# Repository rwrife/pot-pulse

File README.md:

# Pot Pulse

USB-powered ESP32-C3 plant-shelf monitor for home growers to track soil moisture, light, and microclimate trends in a local dashboard without cloud accounts or automatic watering.

## Motivation
Houseplant care is mostly guesswork between watering days. People often overwater because they cannot see trend data (light, moisture, humidity) across multiple pots in one place.

## Target users
- Home plant hobbyists with 1–20 potted indoor plants
- Small office/shared-space plant caretakers
- Makers who want a safe, low-voltage, locally controlled monitoring tool

## Concrete use cases
1. Compare morning/evening light exposure per shelf position.
2. Track soil moisture drop rate after watering to tune intervals.
3. Spot dry microclimates near windows/vents before plants decline.
4. Export a local history snapshot for seasonal care adjustments.

## Intended end-to-end workflow
1. Assemble device (SELV USB only) and connect sensors for each monitored pot zone.
2. Join device to local network (or direct USB setup mode).
3. Name shelves/zones in the companion app.
4. Calibrate moisture probes with dry/wet reference points.
5. Review live status + trend charts; set local reminder thresholds.
6. Export CSV/JSON snapshots for personal records.

## MVP features
- ESP32-C3 firmware with periodic sampling (moisture, light, temp/humidity)
- Local-first companion web app (mobile + desktop browsers)
- Per-zone calibration profiles and health-state bands (informational only)
- On-device ring buffer with timestamped readings
- Local network API for status/history/export
- USB recovery/provisioning flow
- Versioned backup/restore of settings and zone metadata

## Non-goals (MVP)
- Automatic watering, relays, or pumps
- Any mains-voltage control path
- Cloud account requirement or remote telemetry service
- Plant diagnosis/treatment claims
- Outdoor/weatherproof deployment

## Privacy, permissions, and data ownership
- Local-first by default: data stored on device and exported by user action.
- No required cloud service.
- Companion app only requests local-network/browser storage permissions needed for setup, caching, and export.
- User can delete local history and reset device from settings.

## Safety limits
- Prototype scope is **SELV USB power only (5V)**.
- Monitoring only; no high-power actuators.
- Not a life-safety, agricultural compliance, or medical system.

## Source tree and artifact policy
Hardware implementation is delivered as editable KiCad source files (not image-only schematics):

- `hardware/kicad/pot-pulse.kicad_pro`
- `hardware/kicad/pot-pulse.kicad_sch`
- `hardware/kicad/pot-pulse.kicad_pcb`

Final BOM source of truth will live in KiCad schematic symbol properties and be exported to tracked `bom/bom.csv`.

## Current status
- ✅ Repository scaffold and execution backlog created
- ✅ MVP architecture, interface ownership, non-goals, and risk baseline documented in [`docs/architecture.md`](docs/architecture.md)
- ✅ Datasheet-backed critical component selection documented in [`hardware/component-selection.md`](hardware/component-selection.md)
- ✅ Editable KiCad project, DRC/ERC evidence, and pad-net cross-check tooling under [`hardware/kicad/`](hardware/kicad/)
- ✅ Firmware MVP with repeatable native tests and ESP32-C3 builds under [`firmware/`](firmware/)
- ✅ Companion app MVP with repeatable typecheck/test/build under [`app/`](app/)
- ✅ Integration bring-up + assembly docs, evidence matrix, and fabrication preview bundle under [`docs/`](docs/)
- 🚧 Production-ready fabrication release still blocked by open PCB unconnected items (see `docs/evidence/2026-09-14/drc.json`)

## Milestones
1. Architecture and risk baseline
2. Datasheet-backed component selection
3. KiCad schematic and ERC
4. Schematic-source BOM and non-schematic procurement tracking
5. PCB layout and DRC
6. Firmware MVP with repeatable build/tests
7. Companion app MVP with local export
8. Integration docs and fabrication-ready release package

See [`PLAN.md`](PLAN.md) for the authoritative issue dependency graph and exit gates.

## Integration handoff docs

- Bring-up procedure: [`docs/bring-up.md`](docs/bring-up.md)
- Assembly sequence and checks: [`docs/assembly.md`](docs/assembly.md)
- Evidence classification: [`docs/evidence-matrix.md`](docs/evidence-matrix.md)
- Fabrication/release workflow: [`docs/release-artifacts.md`](docs/release-artifacts.md)
- Explicit media placeholders: [`docs/media-placeholders.md`](docs/media-placeholders.md)

## Development quickstart
### Firmware
- Toolchain: PlatformIO (ESP-IDF framework)
- Target: ESP32-C3 dev module + custom carrier pin map

### Companion app
- TypeScript + Vite + local-first PWA behavior
- Connect to device over local HTTP/WebSocket

### Hardware
- KiCad 9 project under `hardware/kicad/`
- BOM exported to `bom/bom.csv`

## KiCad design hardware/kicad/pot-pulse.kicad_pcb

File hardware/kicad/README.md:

# Pot Pulse KiCad project

This directory contains the editable KiCad 9 project for the USB-powered Pot Pulse four-zone sensor node: first-pass schematic (issue #3) and first-pass PCB (issue #5).

## Files

- `pot-pulse.kicad_pro` — KiCad project settings.
- `pot-pulse.kicad_sch` — editable schematic source of truth.
- `pot-pulse.kicad_pcb` — editable first-pass PCB (generated by `build_pcb.py`, routed via FreeRouter, DRC-adjudicated).
- `lib/pot-pulse.kicad_sym` — project symbols whose pin maps were transcribed from the manufacturer documents cited in `../component-selection.md`.
- `lib/pot-pulse.pretty/` — project land patterns (ESP32-C3-MINI-1, VEML7700) transcribed from the datasheets cited in `../component-selection.md`; generated by `generate_footprints.py`.
- `fp-lib-table` / `sym-lib-table` — project library registration so the board opens on any machine with KiCad 9.
- `generate_schematic.py` — reproducible first-capture generator; the generated schematic remains editable in KiCad.
- `validate_schematic.py` — static acceptance checks for required parts, properties, nets, pin mappings, test access, and the native ERC summary.
- `netlist_to_json.py` — exports `reports/pcb-input/{netlist,components}.json` (placement/routing input data derived from the schematic netlist).
- `build_pcb.py` — generates `pot-pulse.kicad_pcb` through the pcbnew API (outline, placement table with courtyard/edge asserts, net classes, RF rule areas, pours, text).
- `generate_footprints.py` — generates the project land patterns from datasheet dimensions.
- `route_driver.py` — Specctra DSN export / SES import driver (import saves immediately before probing).
- `dsn_strip_inner_layers.py` — keeps the autorouter on F.Cu/B.Cu so the inner planes stay solid.
- `rip_up_dangling.py` / `rip_up_zone.py` / `rip_up_congested.py` — stranded-fragment and surgical rip-up helpers between router passes.
- `close_stubs.py` — deterministic final stub closer (collision-capsule tested; `--dry` reports LEFT pairs verbatim).
- `fill_zones.py` — headless "Fill All Zones".
- `silk_hygiene.py` — post-route silkscreen cleanup (hides dense-passive refs, shrinks TP/test refs, enforces 0.15 mm text stroke).
- `reload_probe.py` / `check_placement_vs_table.py` / `board_inventory.py` / `list_plane_tracks.py` / `lane_blockers.py` — verification probes (reload integrity, placement-vs-table drift, copper inventory, residual-gap diagnosis).
- `reports/erc.rpt` — native KiCad 9 electrical-rules report.
- `reports/schematic-analysis.txt` — supplemental static analyzer output.
- `reports/pot-pulse.net` — netlist export feeding `netlist_to_json.py`.
- `reports/drc-placement.json` — placement-stage native DRC (pre-routing).
- `reports/routing/` — per-pass DSN/SES/DRC evidence; each `passN-drc.json` is the `kicad-cli` truth for that pass.
- `reports/drc-final.json` — committed final DRC state for `pot-pulse.kicad_pcb`.

Layout intent, keepout strategy, grounding approach, assembly/testability notes, and documented first-pass gaps: `../pcb-design-notes.md`.

## Reproduce and verify

The host needs KiCad 9 symbol libraries and Python 3.11+:

```sh
python3 -m venv /tmp/pot-pulse-kicad-venv
/tmp/pot-pulse-kicad-venv/bin/pip install -r hardware/kicad/requirements.txt
KICAD_SYMBOL_DIR=/usr/share/kicad/symbols \
  /tmp/pot-pulse-kicad-venv/bin/python hardware/kicad/generate_schematic.py
kicad-cli sch erc -o hardware/kicad/reports/erc.rpt hardware/kicad/pot-pulse.kicad_sch
KICAD_SYMBOL_DIR=/usr/share/kicad/symbols \
  /tmp/pot-pulse-kicad-venv/bin/python hardware/kicad/validate_schematic.py \
  --erc hardware/kicad/reports/erc.rpt
```

The PCB steps need the `pcbnew` Python bindings (KiCad container image); all
scripts run inside `hardware/kicad/`:

```sh
kicad-cli sch export netlist pot-pulse.kicad_sch -o reports/pot-pulse.net
python3 netlist_to_json.py
python3 build_pcb.py                       # asserts courtyard/edge placement
python3 reload_probe.py                    # reload integrity + pad-net probe
python3 check_placement_vs_table.py        # board vs build_pcb.py table
python3 route_driver.py export reports/routing/passN.dsn
# host: java -Djava.awt.headless=true -jar freerouting-2.4.1.jar \
#   -de passN-2l.dsn -do passN.ses -mp 12 -gui.enabled=false   (after dsn_strip_inner_layers.py)
python3 route_driver.py import reports/routing/passN.ses
python3 rip_up_dangling.py && python3 fill_zones.py && python3 silk_hygiene.py
python3 close_stubs.py --drc reports/routing/passN-drc.json    # deterministic final stubs
kicad-cli pcb drc --severity-error --severity-warning --format json \
  --output reports/drc-final.json pot-pulse.kicad_pcb
```

The repository's headless `kicad-cli` wrapper runs KiCad 9 in a container. Committed reports are generated from the editable sources, not hand-authored.

## Evidence boundary

Schematic files provide **static schematic and native ERC evidence**. The PCB
provides **static layout + native DRC evidence plus autorouter-derived routing
provenance**. These files do not provide simulation, assembled-board, EMC,
environmental, field, or calibration evidence. RF keepout geometry is
datasheet-derived; measured RF performance is bench evidence not yet claimed.
USB full-speed impedance is not yet stackup-verified (documented gap in
`../pcb-design-notes.md`).

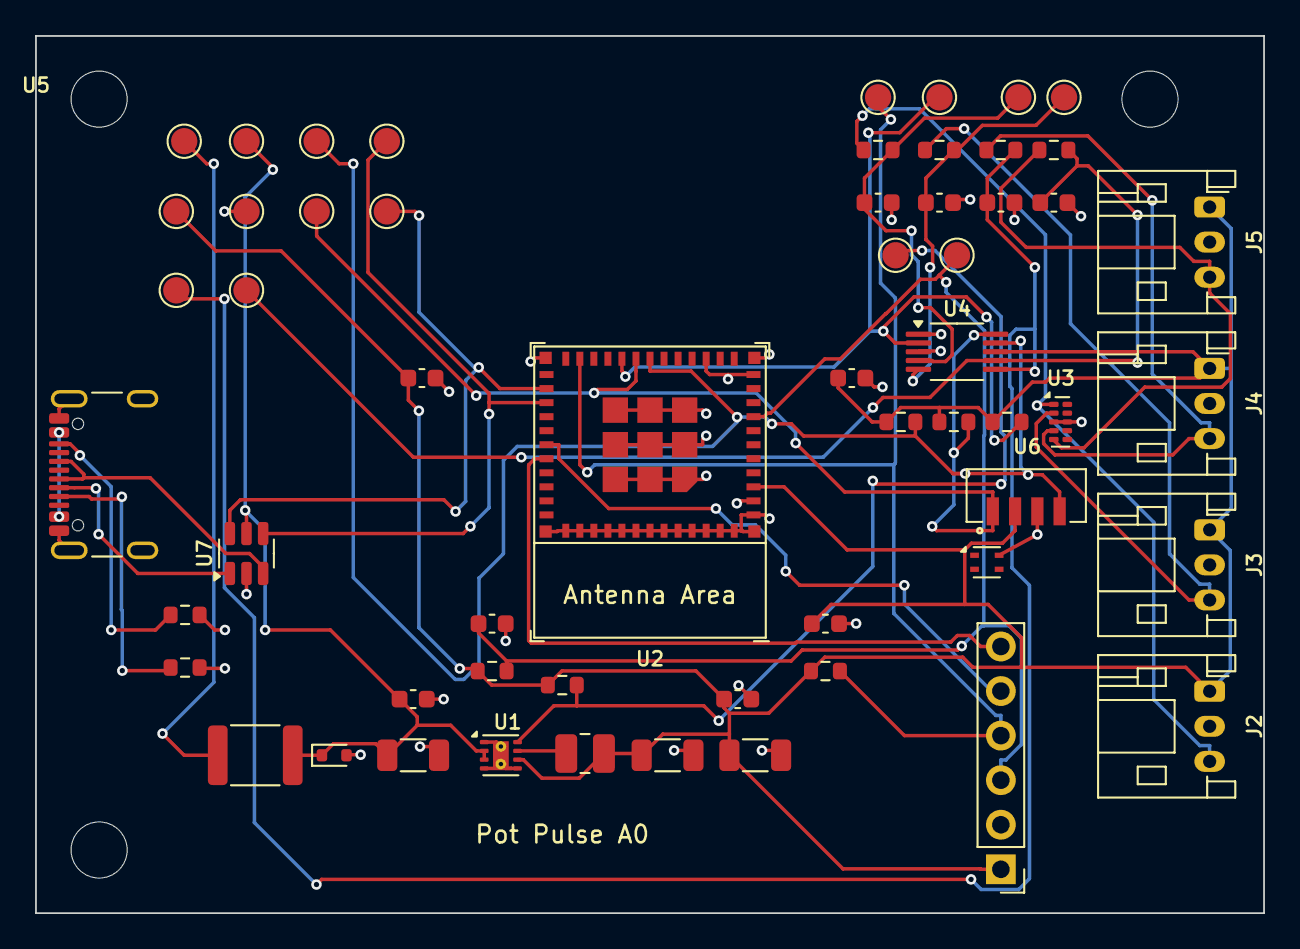
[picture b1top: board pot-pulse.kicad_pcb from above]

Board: 4 copper layers, 70.0 x 50.0 mm, 60 parts (0 on the bottom side), 27 nets.

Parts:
C1, C3, C4: C_1206_3216Metric
C2, C5, C6, C7, C8, C9, C10, C11, C12, C13: C_0603_1608Metric
D1: D_SOD-523
F1: Fuse_1812_4532Metric
J1: USB_C_Receptacle_GCT_USB4105-xx-A_16P_TopMnt_Hori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; USB_C_Receptacle_GCT_USB4105-xx-A_16P_TopMnt_Horizontal
J2, J3, J4, J5: JST_PH_S3B-PH-K_1x03_P2.00mm_Horizontal
J6: PinHeader_1x06_P2.54mm_Vertical
L1: L_1008_2520Metric
MK1, MK2, MK3: MountingHole_3.2mm_M3
R1, R2, R3, R4, R5, R6, R7, R8, R9, R10, R11, R12: R_0603_1608Metric
TP1, TP2, TP3, TP4, TP5, TP6, TP7, TP8, TP9, TP10, TP11, TP12, TP13, TP14, TP15, TP16: TestPoint_Pad_D1.5mm
U1: WSON-8-1EP_2x2mm_P0.5mm_EP0.9x1.6mm_ThermalVias
U2: ESP32-C3-MINI-1
U3: USON-10_2.5x1.0mm_P0.5mm
U4: VSSOP-10_3x3mm_P0.5mm
U5: Sensirion_DFN-4_1.5x1.5mm_P0.8mm_SHT4x_NoCentralP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; Sensirion_DFN-4_1.5x1.5mm_P0.8mm_SHT4x_NoCentralPad
U6: VEML7700
U7: SOT-23-6

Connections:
/+3V3: C3.1, C4.1, C5.1, C7.1, C8.1, C9.1, J2.1, J3.1, J4.1, J5.1, J6.1, L1.2, R3.1, R4.1, R5.1, R6.1, R7.1, R8.1, TP3.1, U1.6, U2.3, U4.8, U5.3, U6.2
/+5V_PROTECTED: C1.1, C2.1, D1.1, F1.2, TP2.1, U1.2, U1.3, U7.5
/ADC_ALERT_N: R8.2, TP12.1, U2.20, U4.2
/BOOT_GPIO9: J6.4, R7.2, TP11.1, U2.23
/CC1: J1.A5, R1.1
/CC2: J1.B5, R2.1
/EN: C6.1, J6.3, R6.2, TP10.1, U2.8
/GND: C1.2, C2.2, C3.2, C4.2, C5.2, C6.2, C7.2, C8.2, C9.2, C10.2, C11.2, C12.2, C13.2, D1.2, J1.A1, J1.A12, J1.B1, J1.B12, J1.S1, J2.2, J3.2, J4.2, J5.2, J6.2, R1.2, R2.2, TP4.1, U1.1, U1.4, U1.5, U1.9, U2.1, U2.2, U2.11, U2.14, U2.36, U2.37, U2.38, U2.39, U2.40, U2.41, U2.42, U2.43, U2.44, U2.45, U2.46, U2.47, U2.48, U2.49, U2.50, U2.51, U2.52, U2.53, U3.3, U3.8, U4.1, U4.3, U5.4, U6.3, U7.2
/I2C_SCL: R5.2, TP6.1, U2.19, U4.10, U5.2, U6.1
/I2C_SDA: R4.2, TP5.1, U2.18, U4.9, U5.1, U6.4
/MOISTURE_AIN0: C10.1, R9.2, TP13.1, U4.4
/MOISTURE_AIN1: C11.1, R10.2, TP14.1, U4.5
/MOISTURE_AIN2: C12.1, R11.2, TP15.1, U4.6
/MOISTURE_AIN3: C13.1, R12.2, TP16.1, U4.7
/PROBE1_RAW: J2.3, R9.1, U3.1
/PROBE2_RAW: J3.3, R10.1, U3.2
/PROBE3_RAW: J4.3, R11.1, U3.4
/PROBE4_RAW: J5.3, R12.1, U3.5
/REG_PG: R3.2, TP9.1, U1.8
/SW_NODE: L1.1, U1.7
/U0RXD: J6.5, U2.30
/U0TXD: J6.6, U2.31
/USB_CONN_DM: J1.A7, J1.B7, U7.1
/USB_CONN_DP: J1.A6, J1.B6, U7.3
/USB_DM: TP8.1, U2.26, U7.6
/USB_DP: TP7.1, U2.27, U7.4
/VBUS: F1.1, J1.A4, J1.A9, J1.B4, J1.B9, TP1.1

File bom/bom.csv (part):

References,Quantity,Value,Footprint,Manufacturer,MPN,Supplier,Supplier PN,Source URL,Estimated Unit Cost USD,Price Snapshot Date,Extended Estimate USD,Pricing Status,Datasheet,Notes
"C1, C4",2,10uF 10V X5R,Capacitor_SMD:C_1206_3216Metric,Murata,GRM31CR61A106KA01L,LCSC,C97949,https://www.lcsc.com/product-detail/C97949.html,0.3352,2026-09-08,0.6704,Dated estimate - recheck before order,https://www.murata.com/en-global/products/capacitor/mlcc/ove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,Buck input bulk capacitor. | ESP32-C3 local rail bulk capacitor.
"C2, C5, C7, C8, C9, C10, C11, C12, C13",9,100nF 50V X7R,Capacitor_SMD:C_0603_1608Metric,Murata,GRM188R71H104KA93D,LCSC,C77055,https://www.lcsc.com/product-detail/C77055.html,0.0199,2026-09-08,0.1791,Dated estimate - recheck before order,https://www.murata.com/en-global/products/capacitor/mlcc/ove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,ADS1115 local VDD bypass per datasheet. | Buck high-frequency input bypass. | ESP32-C3 high-frequency decoupling. | SHT40 local supply decoupling. | VEML7700 local supply decoupling. | Zone 1 ADC shunt filter capacitor; settling to be bench characterized. | Zone 2 ADC shunt filter capacitor; settling to be bench characterized. | Zone 3 ADC shunt filter capacitor; settling to be bench characterized. | Zone 4 ADC shunt filter capacitor; settling to be bench characterized.
C3,1,22uF 16V X5R,Capacitor_SMD:C_1206_3216Metric,Murata,GRM31CR61C226ME15L,Unassigned,,https://www.murata.com/en-global/products/capacitor/mlcc/ove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,TBD - live quote required,2026-09-08,TBD,Quote required,https://www.murata.com/en-global/products/capacitor/mlcc/ove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,Buck output capacitor; 22 µF nominal per TI typical application.
C6,1,1uF 16V X7R,Capacitor_SMD:C_0603_1608Metric,Murata,GRM188R71C105KA12D,Unassigned,,https://www.murata.com/en-global/products/capacitor/mlcc/ove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,TBD - live quote required,2026-09-08,TBD,Quote required,https://www.murata.com/en-global/products/capacitor/mlcc/ove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,EN power-on reset delay capacitor; bench-verify startup timing.
D1,1,ESD5Z5.0T1G,Diode_SMD:D_SOD-523,onsemi,ESD5Z5.0T1G,LCSC,C82044,https://www.lcsc.com/product-detail/C82044.html,0.0365,2026-09-08,0.0365,Dated estimate - recheck before order,https://www.onsemi.com/pdf/datasheet/esd5z2.5t1-d.pdf,5 V VBUS transient clamp after PPTC; short ground return.
F1,1,500mA hold / 1A trip,Fuse:Fuse_1812_4532Metric,Bourns,MF-MSMF050-2,LCSC,C17313,https://www.lcsc.com/product-detail/C17313.html,0.0690,2026-09-08,0.0690,Dated estimate - recheck before order,https://bourns.com/docs/product-datasheets/mf-msmf.pdf,Resettable USB input protection; bench-check radio-burst margin and nuisance trips.
J1,1,USB-C POWER + NATIVE USB,Connector_USB:USB_C_Receptacle_GCT_USB4105-xx-A_16P_TopMnt_Horizontal,Global Connector Technology,USB4105-GF-A,LCSC,C3020560,https://www.lcsc.com/product-detail/C3020560.html,1.0319,2026-09-08,1.0319,Dated estimate - recheck before order,https://gct.co/files/specs/usb4105-spec.pdf,USB 2.0 sink; CC1/CC2 each use 5.1 kΩ Rd; shield tied to GND.
J2,1,ZONE 1 SEN0193,Connector_JST:JST_PH_S3B-PH-K_1x03_P2.00mm_Horizontal,JST,S3B-PH-K-S(LF)(SN),LCSC,C157929,https://www.lcsc.com/product-detail/C157929.html,0.0497,2026-09-08,0.0497,Dated estimate - recheck before order,https://www.jst-mfg.com/product/pdf/eng/ePH.pdf,"Zone 1: pin 1=3V3, pin 2=GND, pin 3=analog signal; verify mating cable orientation before assembly."
J3,1,ZONE 2 SEN0193,Connector_JST:JST_PH_S3B-PH-K_1x03_P2.00mm_Horizontal,JST,S3B-PH-K-S(LF)(SN),LCSC,C157929,https://www.lcsc.com/product-detail/C157929.html,0.0497,2026-09-08,0.0497,Dated estimate - recheck before order,https://www.jst-mfg.com/product/pdf/eng/ePH.pdf,"Zone 2: pin 1=3V3, pin 2=GND, pin 3=analog signal; verify mating cable orientation before assembly."
J4,1,ZONE 3 SEN0193,Connector_JST:JST_PH_S3B-PH-K_1x03_P2.00mm_Horizontal,JST,S3B-PH-K-S(LF)(SN),LCSC,C157929,https://www.lcsc.com/product-detail/C157929.html,0.0497,2026-09-08,0.0497,Dated estimate - recheck before order,https://www.jst-mfg.com/product/pdf/eng/ePH.pdf,"Zone 3: pin 1=3V3, pin 2=GND, pin 3=analog signal; verify mating cable orientation before assembly."
J5,1,ZONE 4 SEN0193,Connector_JST:JST_PH_S3B-PH-K_1x03_P2.00mm_Horizontal,JST,S3B-PH-K-S(LF)(SN),LCSC,C157929,https://www.lcsc.com/product-detail/C157929.html,0.0497,2026-09-08,0.0497,Dated estimate - recheck before order,https://www.jst-mfg.com/product/pdf/eng/ePH.pdf,"Zone 4: pin 1=3V3, pin 2=GND, pin 3=analog signal; verify mating cable orientation before assembly."
L1,1,2.2uH 1.3A,Inductor_SMD:L_1008_2520Metric,TDK,VLS252012T-2R2M1R3,Unassigned,,https://product.tdk.com/en/search/inductor/inductor/smd/info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,TBD - live quote required,2026-09-08,TBD,Quote required,https://product.tdk.com/en/search/inductor/inductor/smd/info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,Datasheet-recommended TPS6216x inductor; verify saturation margin in layout/power review.
"R1, R2",2,5.1k 1%,Resistor_SMD:R_0603_1608Metric,Yageo,RC0603FR-075K1L,LCSC,C105580,https://www.lcsc.com/product-detail/C105580.html,0.0020,2026-09-08,0.0040,Dated estimate - recheck before order,https://www.yageo.com/upload/media/product/productsearch/dat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,USB-C CC1 Rd to GND. | USB-C CC2 Rd to GND.
R3,1,100k 1%,Resistor_SMD:R_0603_1608Metric,Yageo,RC0603FR-07100KL,LCSC,C14675,https://www.lcsc.com/product-detail/C14675.html,0.0022,2026-09-08,0.0022,Dated estimate - recheck before order,https://www.yageo.com/upload/media/product/productsearch/dat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,TPS62162 open-drain PG pull-up.
"R4, R5",2,4.7k 1%,Resistor_SMD:R_0603_1608Metric,Yageo,RC0603FR-074K7L,LCSC,C99782,https://www.lcsc.com/product-detail/C99782.html,0.0023,2026-09-08,0.0046,Dated estimate - recheck before order,https://www.yageo.com/upload/media/product/productsearch/dat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,Single assembled I2C SCL pull-up to 3V3. | Single assembled I2C SDA pull-up to 3V3.
"R6, R7, R8",3,10k 1%,Resistor_SMD:R_0603_1608Metric,Yageo,RC0603FR-0710KL,LCSC,C98220,https://www.lcsc.com/product-detail/C98220.html,0.0023,2026-09-08,0.0069,Dated estimate - recheck before order,https://www.yageo.com/upload/media/product/productsearch/dat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,ADS1115 ALERT/RDY open-drain pull-up. | EN pull-up; EN must not float. | GPIO9 boot-strapping pull-up; debug header can pull low.
"R9, R10, R11, R12",4,1k 1%,Resistor_SMD:R_0603_1608Metric,Yageo,RC0603FR-071KL,LCSC,C22548,https://www.lcsc.com/product-detail/C22548.html,0.0021,2026-09-08,0.0084,Dated estimate - recheck before order,https://www.yageo.com/upload/media/product/productsearch/dat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,Zone 1 ADC series filter resistor after ESD. | Zone 2 ADC series filter resistor after ESD. | Zone 3 ADC series filter resistor after ESD. | Zone 4 ADC series filter resistor after ESD.
U1,1,TPS62162DSGR 3.3V,Package_SON:WSON-8-1EP_2x2mm_P0.5mm_EP0.9x1.6mm_ThermalVias,Texas Instruments,TPS62162DSGR,LCSC,C40256,https://www.lcsc.com/product-detail/C40256.html,0.9697,2026-09-08,0.9697,Dated estimate - recheck before order,https://www.ti.com/lit/ds/symlink/tps62160.pdf,Fixed 3.3 V buck; FB and exposed pad to AGND; short SW loop required.
U2,1,ESP32-C3-MINI-1-H4X,pot-pulse:ESP32-C3-MINI-1,Espressif Systems,ESP32-C3-MINI-1-H4X,LCSC,C41349510,https://www.lcsc.com/product-detail/C41349510.html,3.0795,2026-09-08,3.0795,Dated estimate - recheck before order,https://www.espressif.com/sites/default/files/documentation/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,4 MB H4X module; native USB on GPIO18/19; antenna keepout is mandatory.
U3,1,TPD4E05U06DQAR,Package_SON:USON-10_2.5x1.0mm_P0.5mm,Texas Instruments,TPD4E05U06DQAR,LCSC,C138714,https://www.lcsc.com/product-detail/C138714.html,0.0819,2026-09-05,0.0819,Dated estimate - recheck before order,https://www.ti.com/lit/ds/symlink/tpd4e05u06.pdf,Four low-leakage ESD channels at probe connector boundary.
U4,1,ADS1115IDGSR,Package_SO:VSSOP-10_3x3mm_P0.5mm,Texas Instruments,ADS1115IDGSR,LCSC,C37593,https://www.lcsc.com/product-detail/C37593.html,1.5342,2026-09-08,1.5342,Dated estimate - recheck before order,https://www.ti.com/lit/ds/symlink/ads1115.pdf,ADDR=GND gives 0x48; four independent single-ended probe channels.
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
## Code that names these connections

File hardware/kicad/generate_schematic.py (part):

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    capacitor("C6", "1uF 16V X7R", (227, 27), "GRM188R71C105KA12D", "EN power-on reset delay capacitor; bench-verify startup timing.")
    resistor("R7", "10k 1%", (239, 27), "RC0603FR-0710KL", "GPIO9 boot-strapping pull-up; debug header can pull low.")
    add("Connector_Generic:Conn_01x06", "J6", "DEBUG / PROGRAM PADS", (286, 45), "Connector_PinHeader_2.54mm:PinHeader_1x06_P2.54mm_Vertical",
        "N/A", "PCB_DEBUG_PADS", "~", "Unpopulated labeled pads: 3V3, GND, EN, BOOT, U0RXD and U0TXD.", in_bom=False)

    # Four external probes, connector-boundary ESD and per-channel RC filters.
    add("pot-pulse:TPD4E05U06DQAR", "U3", "TPD4E05U06DQAR", (80, 148), "Package_SON:USON-10_2.5x1.0mm_P0.5mm",
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    for pin in ("A4", "A9", "B4", "B9"): connect("J1", pin, "VBUS")
    for pin in ("A1", "A12", "B1", "B12", "S1"): connect("J1", pin, "GND")
    connect("J1", "A5", "CC1"); connect("J1", "B5", "CC2")
    for pin in ("A6", "B6"): connect("J1", pin, "USB_CONN_DP")
    for pin in ("A7", "B7"): connect("J1", pin, "USB_CONN_DM")
    for pin in ("A8", "B8"): nc("J1", pin)
    connect("R1", "1", "CC1"); connect("R1", "2", "GND")
    connect("R2", "1", "CC2"); connect("R2", "2", "GND")
    connect("F1", "1", "VBUS"); connect("F1", "2", "+5V_PROTECTED")
    connect("D1", "1", "+5V_PROTECTED"); connect("D1", "2", "GND")
    for pin, net in {"1":"USB_CONN_DM", "6":"USB_DM", "3":"USB_CONN_DP", "4":"USB_DP", "2":"GND", "5":"+5V_PROTECTED"}.items(): connect("U7", pin, net)

    for pin, net in {"1":"GND", "2":"+5V_PROTECTED", "3":"+5V_PROTECTED", "4":"GND", "5":"GND", "6":"+3V3", "7":"SW_NODE", "8":"REG_PG", "9":"GND"}.items(): connect("U1", pin, net)
    connect("L1", "1", "SW_NODE"); connect("L1", "2", "+3V3")
    for ref in ("C1", "C2"): connect(ref, "1", "+5V_PROTECTED"); connect(ref, "2", "GND")
    connect("C3", "1", "+3V3"); connect("C3", "2", "GND")
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
    connect("U2", "3", "+3V3")
    connect("U2", "8", "EN")
    gpio_nets = {18:"I2C_SDA", 19:"I2C_SCL", 20:"ADC_ALERT_N", 23:"BOOT_GPIO9",
                 26:"USB_DM", 27:"USB_DP", 30:"U0RXD", 31:"U0TXD"}
    for pin, net in gpio_nets.items(): connect("U2", str(pin), net)
    for pin in (5, 6, 12, 13, 16, 21, 22): nc("U2", str(pin))
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    for ref in ("C4", "C5"): connect(ref, "1", "+3V3"); connect(ref, "2", "GND")
    connect("R6", "1", "+3V3"); connect("R6", "2", "EN")
    connect("C6", "1", "EN"); connect("C6", "2", "GND")
    connect("R7", "1", "+3V3"); connect("R7", "2", "BOOT_GPIO9")
    for pin, net in {"1":"+3V3", "2":"GND", "3":"EN", "4":"BOOT_GPIO9", "5":"U0RXD", "6":"U0TXD"}.items(): connect("J6", pin, net)

    for idx in range(1, 5):
        j = f"J{idx+1}"; raw = f"PROBE{idx}_RAW"; adc = f"MOISTURE_AIN{idx-1}"
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    connect("U3", "3", "GND"); connect("U3", "8", "GND")
    for pin in (6, 7, 9, 10): nc("U3", str(pin))

    for pin, net in {"1":"GND", "2":"ADC_ALERT_N", "3":"GND", "4":"MOISTURE_AIN0", "5":"MOISTURE_AIN1", "6":"MOISTURE_AIN2", "7":"MOISTURE_AIN3", "8":"+3V3", "9":"I2C_SDA", "10":"I2C_SCL"}.items(): connect("U4", pin, net)
    connect("C7", "1", "+3V3"); connect("C7", "2", "GND")
    connect("R8", "1", "+3V3"); connect("R8", "2", "ADC_ALERT_N")
    connect("R4", "1", "+3V3"); connect("R4", "2", "I2C_SDA")
    connect("R5", "1", "+3V3"); connect("R5", "2", "I2C_SCL")
    for pin, net in {"1":"I2C_SDA", "2":"I2C_SCL", "3":"+3V3", "4":"GND"}.items(): connect("U5", pin, net)
    connect("C8", "1", "+3V3"); connect("C8", "2", "GND")
    for pin, net in {"1":"I2C_SCL", "2":"+3V3", "3":"GND", "4":"I2C_SDA"}.items(): connect("U6", pin, net)
    connect("C9", "1", "+3V3"); connect("C9", "2", "GND")

    # ERC source declarations and named test access.
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            "ERC-only source declaration; not a purchased component.", in_bom=False)
        connect(ref, "1", net)
    test_nets = ["VBUS", "+5V_PROTECTED", "+3V3", "GND", "I2C_SDA", "I2C_SCL", "USB_DP", "USB_DM",
                 "REG_PG", "EN", "BOOT_GPIO9", "ADC_ALERT_N", "MOISTURE_AIN0", "MOISTURE_AIN1", "MOISTURE_AIN2", "MOISTURE_AIN3"]
    for idx, net in enumerate(test_nets, 1):
        ref = f"TP{idx}"
        add("Connector:TestPoint", ref, net, (28 + ((idx-1) % 8) * 35, 215 + ((idx-1)//8)*14),
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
